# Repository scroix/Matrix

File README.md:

# eTextile matrix sensor / V1.0 Extension board with builtin Teensy 3.2
### Transforming textiles into an intuitive way to interact with computers
#### This project is part of an electronic textiles research on HCI gesture interaction that was started in 2005

- Author: Maurin Donneaud <maurin@etextile.org>
- Repository: https://github.com/eTextile/Matrix/tree/teensy_matrix
- Project web page: http://matrix.eTextile.org
- License: CC-BY-SA (see the License file)

## About The project
Using a fabric to sense the touch is now possible with the E256 eTextile matrix sensor.
The E256 is a development kit for designers, makers and companies who want to combine textile and programing into new eTextile projects. From the beginning this project stimulates the development of technologies in artistic use cases: playing music, combine graphics and sound, creating textile furniture that can have tactile properties, etc, etc.

This kit features 30cm by 30cm sensitive textile that allow multi-touch sensing and pressures topographic analysis.
The software, frmware and hardware are distributed under Creative Commons license (Cf: LICENSE.txt). The E256 firmware is made with Arduino IDE. BLE hardware is the next step to interface the E256-textile with mobile devices. Made out of conductive textile shaped in rows and columns and a layer of piezoresistive fabric, the E256-textile sensor is designed to be easy to make.

## Project content
- Arduino firmware : Teensy 3.1, 3.2, 4.0(TODO)
- PCB made with [KiCad](https://kicad-pcb.org/)
- eTextile matrix sensor HOWTO
- Real time 3D visualization using [openFrameworks](https://www.openframeworks.cc/)
- Audio players running on Raspberry and Bela-mini using [libPd](https://github.com/libpd)
- Same players can be lodded on PC with PureData Vanilla (http://msp.ucsd.edu/software.html)

## Publications
- [NIME17](http://www.nime2017.org/) - Designing a Multi-Touch eTextile for Music Performances.
- Maurin Donneaud, Cedric Honnet, Paul Strohmeier
  - [Paper](https://etextile.github.io/resistiveMatrix/publications/NIME17-eTextile.pdf) - [Video](https://vimeo.com/217690743)
- [MOCO17](http://moco17.movementcomputing.org/) - Music Skin: Fabric Interface for Expressive Music Control.
- Maurin Donneaud, Cedric Honnet, Paul Strohmeier
  - [Paper](https://etextile.github.io/resistiveMatrix/publications/MOCO17-MusicSkin.pdf)

## Docs
- [A video made at Schmiede 2014](http://www.kobakant.at/DIY/?p=4305/)
- [Pictures of the project and context](https://www.flickr.com/photos/maurin/albums/72157673740361510)

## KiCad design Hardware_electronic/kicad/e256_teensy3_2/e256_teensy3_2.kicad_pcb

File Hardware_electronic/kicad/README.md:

# eTextile matrix sensor
### Transforming textiles into an intuitive way to interact with computers
#### This project is part of an electronic textiles research on HCI gesture interaction that was started in 2005

- Author: Maurin Donneaud <maurin@etextile.org>
- Repository: https://github.com/eTextile/Matrix/tree/teensy_matrix
- Project web page: http://matrix.eTextile.org
- License: CC-BY-SA (see the License file)

### Eagle
This file is contanoing a PCB with eTextile bus connector - V1

### KiCad 
the textile bus systhem is not a maket productso I switch to the - V2

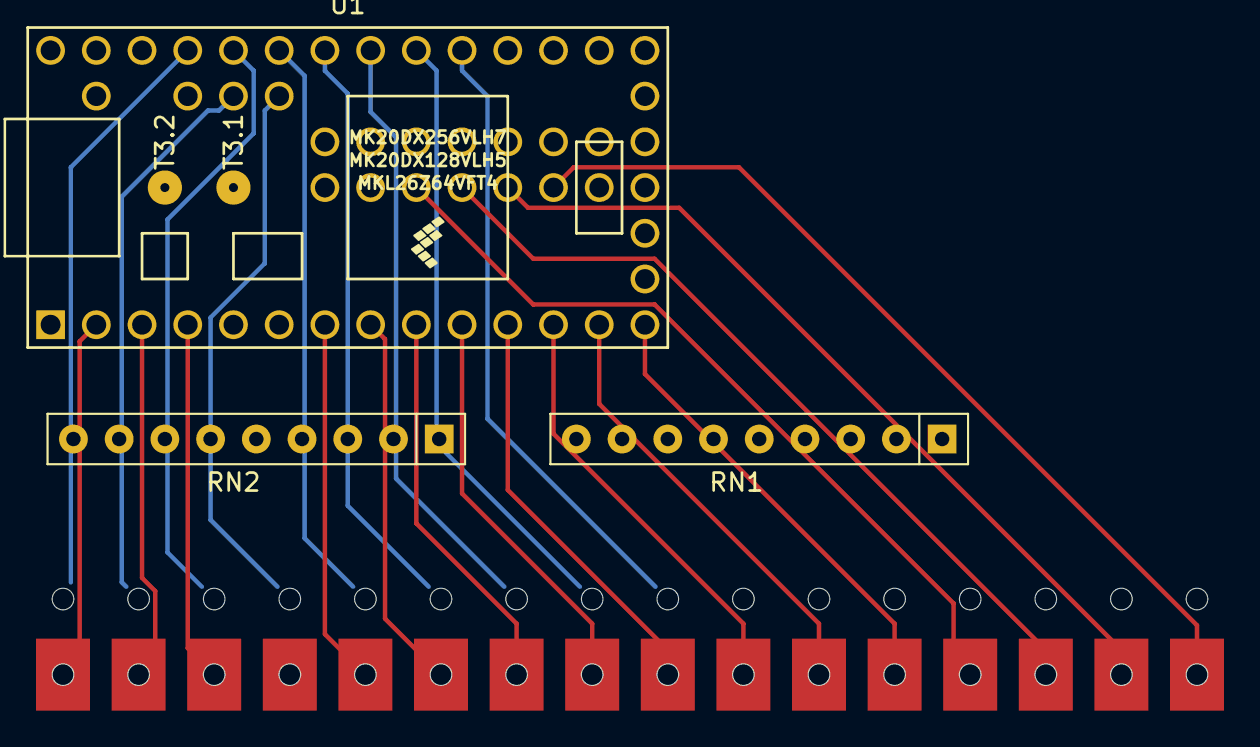
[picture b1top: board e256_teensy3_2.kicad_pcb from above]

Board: 2 copper layers, 4 parts (0 on the bottom side), 31 nets.

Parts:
RN1, RN2: R_Network08_US; R_Array_SIP9
U1: Teensy3.2; Teensy30_31_32_LC
U2: e256_pad_16x16; e256_pad_16X16

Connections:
COL_0: RN1.2, U1.46, U2.16
COL_1: RN1.3, U1.47, U2.17
COL_2: RN1.4, U1.48, U2.18
COL_3: RN1.5, U1.49, U2.19
COL_4: RN1.6, U1.14, U2.20
COL_5: RN1.7, U1.13, U2.21
COL_6: RN1.8, U1.12, U2.22
COL_7: RN1.9, U1.11, U2.23
COL_8: RN2.2, U1.10, U2.24
COL_9: RN2.3, U1.9, U2.25
COL_10: RN2.4, U1.8, U2.26
COL_11: RN2.5, U1.7, U2.27
COL_12: RN2.6, U1.40, U2.28
COL_13: RN2.7, U1.4, U2.29
COL_14: RN2.8, U1.3, U2.30
COL_15: RN2.9, U1.2, U2.31
GNDREF: RN1.1, RN2.1, U1.1
ROW_0: U1.45, U2.0
ROW_1: U1.44, U2.1
ROW_2: U1.43, U2.2
ROW_3: U1.21, U2.3
ROW_4: U1.42, U2.4
ROW_5: U1.22, U2.5
ROW_6: U1.23, U2.6
ROW_7: U1.24, U2.7
ROW_10: U1.27, U2.10
ROW_11: U1.28, U2.11
ROW_12: U1.37, U2.12
ROW_13: U1.29, U2.13
ROW_14: U1.36, U2.14
ROW_15: U1.30, U2.15

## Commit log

2018-05-18 Added Firmware/MAIN/build-teensy31/
2018-05-18 Added files
2018-11-21 Minor change
2019-05-09 Updated to work with ESP8266
2019-05-15 Working prototype but the WIFI is to slow
2019-05-15 Update content for ESP8266
2019-05-15 New driver for E256-OSC-WIFI
2019-05-15 Added datasheet
2019-05-16 Minor changes
2019-05-16 Improved latency
2019-11-04 Removed old version (without blob detection)
2019-11-04 Added new firmware with blob detection
2019-11-04 Added new file - still need to rebuild PCB with new eTextile connector
2019-11-04 Updated OpenFrameworks to work with new Arduino Firmware
2019-12-03 Renaming file
2019-12-03 Removed bad file
2019-12-03 Updated for new design
2019-12-03 Updated repo web link
2019-12-05 Updated for new pcb design
2019-12-05 Added private file
2019-12-07 Adde pins under PCB to the Teensy lib
2019-12-08 Moved Lib file to make it global
2019-12-08 Renaming
2019-12-08 Updated path
2019-12-08 Added submodules
2019-12-10 Added V1.2 version - working prototype
2019-12-10 Updated weblink
2019-12-10 Added new README file for the electronic hardware PCBs
2019-12-10 new file
2019-12-11 Updated for new E256 pcb
2019-12-16 Added kicad local ath def
2019-12-16 Removed submodules
2019-12-16 Removed sub_mod
2019-12-16 CleanUP
2019-12-17 Set ADC to 8bit
2020-02-04 Updated URL
2020-04-25 Added device name E256
2020-04-25 Added MIDI
2020-04-25 Removed OSC driver
2020-04-25 Renamed file
2020-04-25 RAZ file
